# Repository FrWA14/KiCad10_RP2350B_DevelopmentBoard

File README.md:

# Carte de développement RP2350B

Carte basée sur le microcontrôleur RP2350B (QFN-80) de Raspberry Pi, conçue sous KiCad 10.

## Modèle 3D

- [`RP2350.stl`](RP2350.stl) : cliquer dessus pour faire tourner la carte en 3D directement
  sur GitHub.
- [`RP2350.step`](RP2350.step) : modèle complet (carte et composants) pour FreeCAD,
  Fusion 360, SolidWorks, etc.

## Ouvrir le projet

Ouvrir `RP2350.kicad_pro` avec KiCad 10. Le projet est autonome : aucune bibliothèque
à installer.

- `libs/RP2350.kicad_sym` : tous les symboles du schéma.
- `libs/RP2350.pretty` : toutes les empreintes du PCB.
- `libs/3dmodels` : les modèles 3D, liés via `${KIPRJMOD}`.

Les tables `sym-lib-table` et `fp-lib-table` du projet déclarent ces bibliothèques en
chemin relatif.

L'inductance L1 (empreinte 0806) utilise le modèle 3D d'une 0805 (`L_0805_2012Metric`).

## Fabrication

Le dossier `production/` contient les fichiers pour JLCPCB : `RP2350_corrected.zip`
(Gerbers et perçages, avec sérigraphie couleur), `bom.csv`, `positions.csv`, ainsi que
les aperçus des deux faces.

La sérigraphie couleur est générée avec le plugin [Fabrication Toolkit Color](https://github.com/FrWA14/KiCad10_Fabrication-Toolkit-Color). Ses réglages
sont dans `fabrication-toolkit-options.json` et les images sources dans `Image/`.
À la commande : PCB blanc, finition ENIG, option « EasyEDA multi-color silkscreen ».

## Licences des bibliothèques

Le symbole, l'empreinte et le modèle 3D du RP2350B viennent de la bibliothèque
RP2350_KiCad, sous licence GPL v3 (`libs/licences/`). Les autres composants viennent des
bibliothèques officielles de KiCad ou des fabricants.

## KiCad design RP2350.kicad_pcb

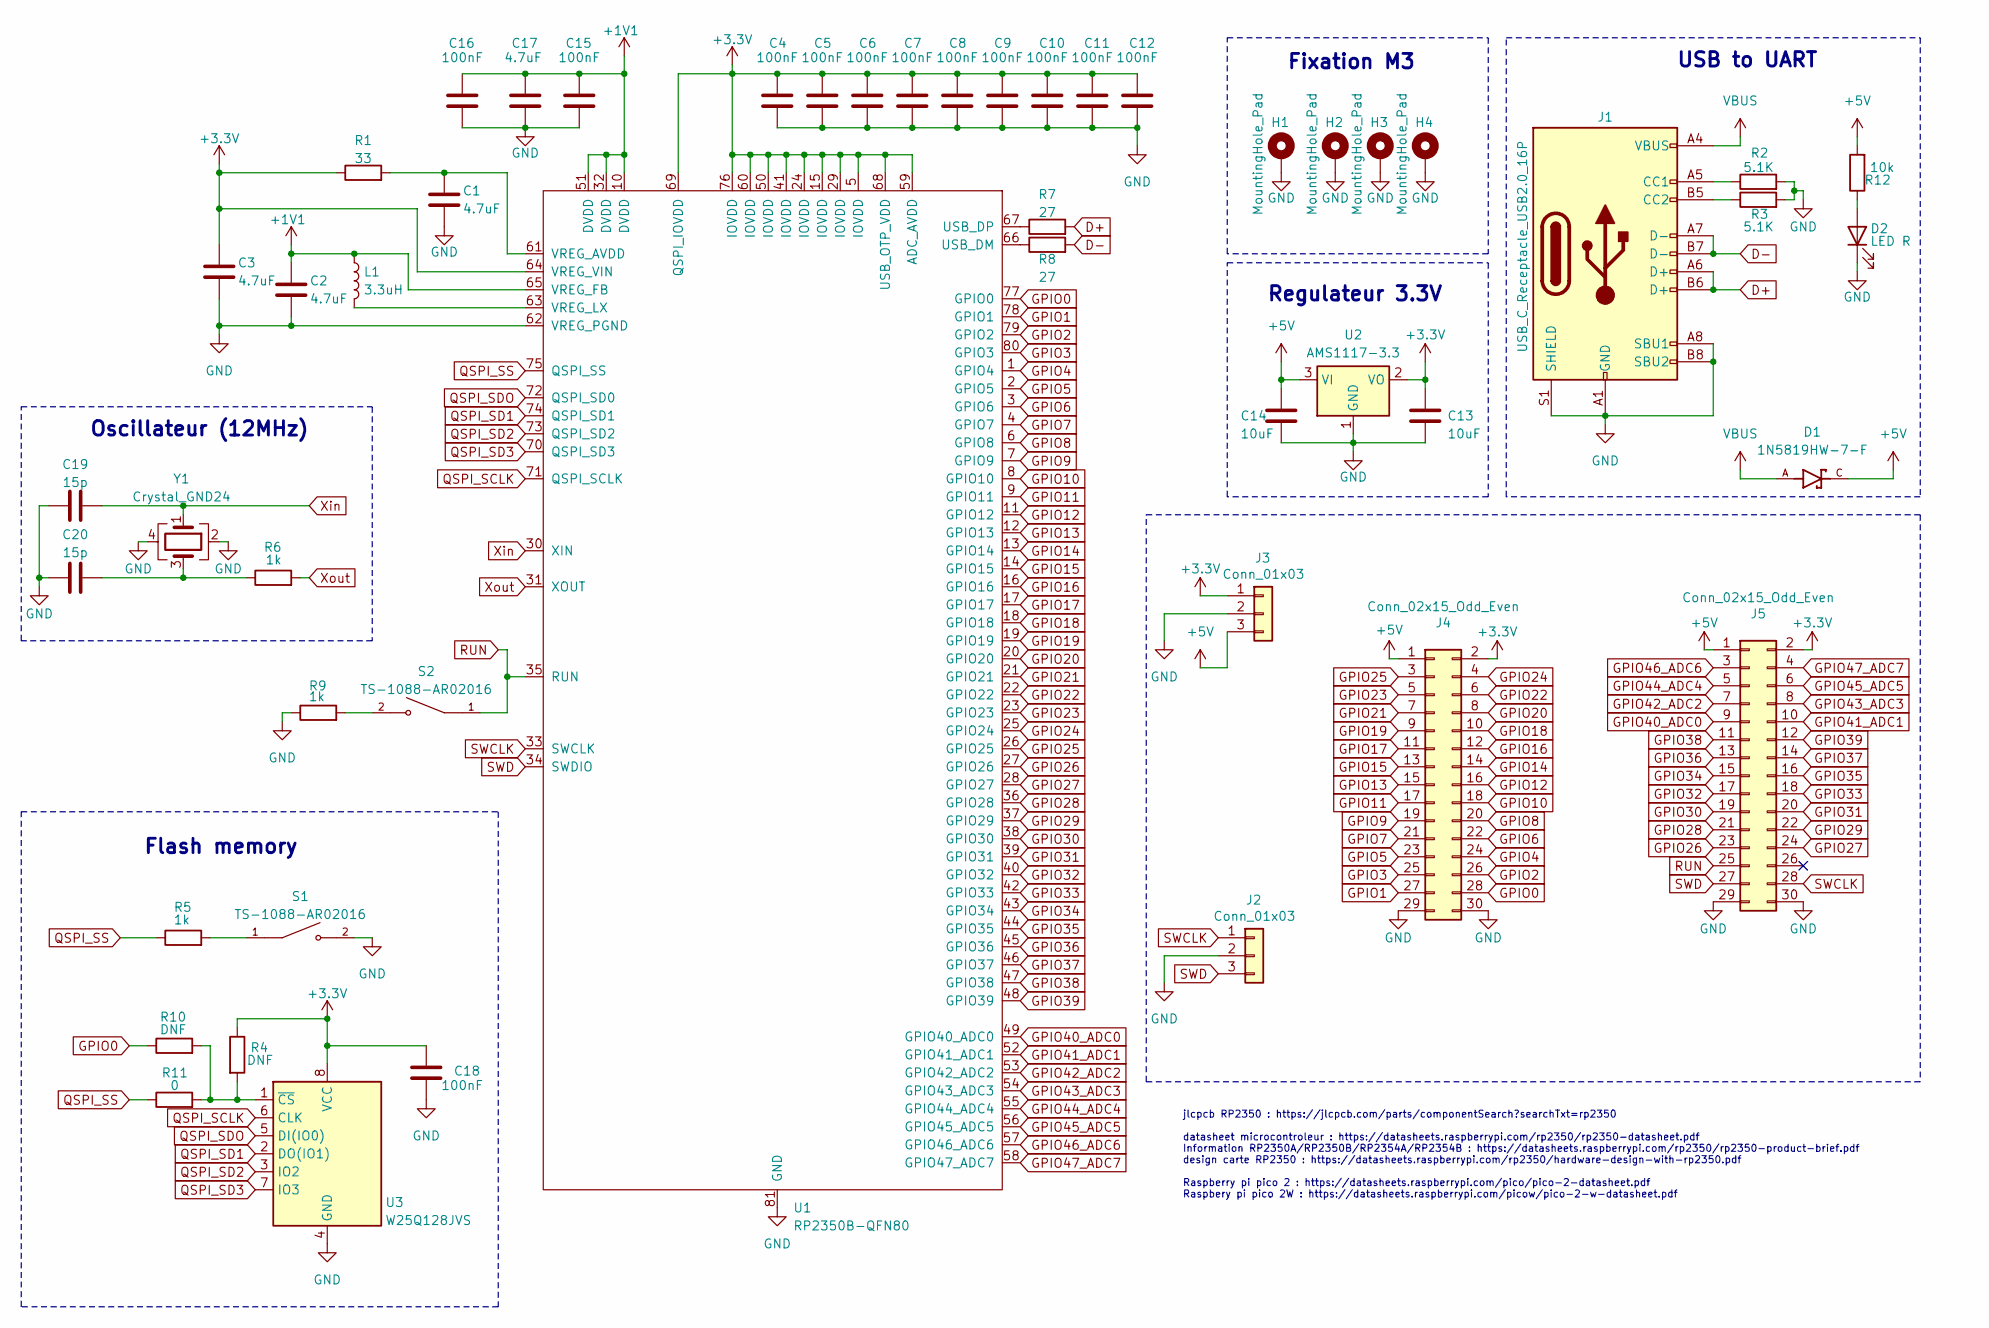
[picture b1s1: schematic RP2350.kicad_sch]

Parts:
C1, C2, C3, C17: 4.7uF; C_0603_1608Metric; JLCPCB Part # C19666
C4, C5, C6, C7, C8, C9, C10, C11, C12, C15, C16, C18: 100nF; C_0603_1608Metric; JLCPCB Part # C14663
C13, C14: 10uF; C_0603_1608Metric; JLCPCB Part # C1691
C19, C20: 15p; C_0603_1608Metric; JLCPCB Part # C1644
D1: 1N5819HW-7-F; D_SOD-123_1N5819HW-7-F; PARTREV 18-2; JLCPCB Part # C82544
D2: LED R; LED_0603_1608Metric; JLCPCB Part # C965799
H1, H2, H3, H4: MountingHole_Pad; MountingHole_3.2mm_M3_Pad_Via
J1: USB_C_Receptacle_USB2.0_16P; USB_C_Receptacle_HCTL_HC-TYPE-C-16P-01A; JLCPCB Part # C393939
J2, J3: Conn_01x03; PinHeader_1x03_P2.54mm_Vertical
J4, J5: Conn_02x15_Odd_Even; IDC-Header_2x15_P2.54mm_Horizontal_vertical; JLCPCB Part # C221084
L1: 3.3uH; L_0806_2016Metric; JLCPCB Part # C42411119
R1: 33; R_0603_1608Metric; JLCPCB Part # C23140
R2, R3: 5.1K; R_0603_1608Metric; JLCPCB Part # C23186
R4, R10: DNF; R_0603_1608Metric
R5, R6, R9: 1k; R_0603_1608Metric; JLCPCB Part # C21190
R7, R8: 27; R_0603_1608Metric; JLCPCB Part # C137753
R11: 0; R_0603_1608Metric; JLCPCB Part # C21189
R12: 10k; R_0603_1608Metric; JLCPCB Part # C25804
S1, S2: TS-1088-AR02016; SW_TS-1088-AR02016; PARTREV N/A; JLCPCB Part # C720477
U1: RP2350B-QFN80; RP2350B_QFN-80_EP_10.573x10.573_Pitch0.4mm; JLCPCB Part # C42415655
U2: AMS1117-3.3; SOT-223-3_TabPin2; JLCPCB Part # C6186
U3: W25Q128JVS; SOIC-8_5.23x5.23mm_P1.27mm; JLCPCB Part # C97521
Y1: Crystal_GND24; Crystal_SMD_3225-4Pin_3.2x2.5mm; JLCPCB Part # C20625731

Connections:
+1V1: C2.1, C15.1, C16.1, C17.1, L1.1, U1.10 (DVDD), U1.32 (DVDD), U1.51 (DVDD), U1.65 (VREG_FB)
+3.3V: C3.1, C4.1, C5.1, C6.1, C7.1, C8.1, C9.1, C10.1, C11.1, C12.1, C13.1, C18.1, J3.1, J4.2, J5.2, R1.1, R4.1, U1.5 (IOVDD), U1.15 (IOVDD), U1.24 (IOVDD), U1.29 (IOVDD), U1.41 (IOVDD), U1.50 (IOVDD), U1.59 (ADC_AVDD), U1.60 (IOVDD), U1.64 (VREG_VIN), U1.68 (USB_OTP_VDD), U1.69 (QSPI_IOVDD), U1.76 (IOVDD), U2.2 (VO), U3.8 (VCC)
+5V: C14.1, D1.C, J3.3, J4.1, J5.1, R12.2, U2.3 (VI)
D+: J1.A6 (D+), J1.B6 (D+), R7.2
D-: J1.A7 (D-), J1.B7 (D-), R8.2
GND: C1.2, C2.2, C3.2, C4.2, C5.2, C6.2, C7.2, C8.2, C9.2, C10.2, C11.2, C12.2, C13.2, C14.2, C15.2, C16.2, C17.2, C18.2, C19.1, C20.1, D2.1 (K), H1.1 (1_1), H2.1 (1_1), H3.1 (1_1), H4.1 (1_1), J1.A1 (GND), J1.A8 (SBU1), J1.A12 (GND), J1.B1 (GND), J1.B8 (SBU2), J1.B12 (GND), J1.S1 (SHIELD), J2.2, J3.2, J4.29, J4.30, J5.29, J5.30, R2.2, R3.2, R9.1, S1.2, U1.62 (VREG_PGND), U1.81 (GND), U2.1 (GND), U3.4 (GND), Y1.2, Y1.4
GPIO0: J4.28, R10.1, U1.77 (GPIO0)
GPIO1: J4.27, U1.78 (GPIO1)
GPIO2: J4.26, U1.79 (GPIO2)
GPIO3: J4.25, U1.80 (GPIO3)
GPIO4: J4.24, U1.1 (GPIO4)
GPIO5: J4.23, U1.2 (GPIO5)
GPIO6: J4.22, U1.3 (GPIO6)
GPIO7: J4.21, U1.4 (GPIO7)
GPIO8: J4.20, U1.6 (GPIO8)
GPIO9: J4.19, U1.7 (GPIO9)
GPIO10: J4.18, U1.8 (GPIO10)
GPIO11: J4.17, U1.9 (GPIO11)
GPIO12: J4.16, U1.11 (GPIO12)
GPIO13: J4.15, U1.12 (GPIO13)
GPIO14: J4.14, U1.13 (GPIO14)
GPIO15: J4.13, U1.14 (GPIO15)
GPIO16: J4.12, U1.16 (GPIO16)
GPIO17: J4.11, U1.17 (GPIO17)
GPIO18: J4.10, U1.18 (GPIO18)
GPIO19: J4.9, U1.19 (GPIO19)
GPIO20: J4.8, U1.20 (GPIO20)
GPIO21: J4.7, U1.21 (GPIO21)
GPIO22: J4.6, U1.22 (GPIO22)
GPIO23: J4.5, U1.23 (GPIO23)
GPIO24: J4.4, U1.25 (GPIO24)
GPIO25: J4.3, U1.26 (GPIO25)
GPIO26: J5.23, U1.27 (GPIO26)
GPIO27: J5.24, U1.28 (GPIO27)
GPIO28: J5.21, U1.36 (GPIO28)
GPIO29: J5.22, U1.37 (GPIO29)
GPIO30: J5.19, U1.38 (GPIO30)
GPIO31: J5.20, U1.39 (GPIO31)
GPIO32: J5.17, U1.40 (GPIO32)
GPIO33: J5.18, U1.42 (GPIO33)
GPIO34: J5.15, U1.43 (GPIO34)
GPIO35: J5.16, U1.44 (GPIO35)
GPIO36: J5.13, U1.45 (GPIO36)
GPIO37: J5.14, U1.46 (GPIO37)
GPIO38: J5.11, U1.47 (GPIO38)
GPIO39: J5.12, U1.48 (GPIO39)
GPIO40_ADC0: J5.9, U1.49 (GPIO40_ADC0)
GPIO41_ADC1: J5.10, U1.52 (GPIO41_ADC1)
GPIO42_ADC2: J5.7, U1.53 (GPIO42_ADC2)
GPIO43_ADC3: J5.8, U1.54 (GPIO43_ADC3)
GPIO44_ADC4: J5.5, U1.55 (GPIO44_ADC4)
GPIO45_ADC5: J5.6, U1.56 (GPIO45_ADC5)
GPIO46_ADC6: J5.3, U1.57 (GPIO46_ADC6)
GPIO47_ADC7: J5.4, U1.58 (GPIO47_ADC7)
unnamed: C20.2, R6.1, Y1.3
unnamed: D2.2 (A), R12.1
unnamed: J1.A5 (CC1), R2.1
unnamed: J1.B5 (CC2), R3.1
unnamed: R5.2, S1.1
unnamed: R9.2, S2.2
unnamed: R8.1, U1.66 (USB_DM)
unnamed: R7.1, U1.67 (USB_DP)
unnamed: C1.1, R1.2, U1.61 (VREG_AVDD)
unnamed: L1.2, U1.63 (VREG_LX)
unnamed: R4.2, R10.2, R11.2, U3.1 (~CS)
QSPI_SCLK: U1.71 (QSPI_SCLK), U3.6 (CLK)
QSPI_SD1: U1.74 (QSPI_SD1), U3.2 (DO(IO1))
QSPI_SD2: U1.73 (QSPI_SD2), U3.3 (IO2)
QSPI_SD3: U1.70 (QSPI_SD3), U3.7 (IO3)
QSPI_SDO: U1.72 (QSPI_SD0), U3.5 (DI(IO0))
QSPI_SS: R5.1, R11.1, U1.75 (QSPI_SS)
RUN: J5.25, S2.1, U1.35 (RUN)
SWCLK: J2.1, J5.28, U1.33 (SWCLK)
SWD: J2.3, J5.27, U1.34 (SWDIO)
VBUS: D1.A, J1.A4 (VBUS), J1.A9 (VBUS), J1.B4 (VBUS), J1.B9 (VBUS)
Xin: C19.2, U1.30 (XIN), Y1.1
Xout: R6.2, U1.31 (XOUT)

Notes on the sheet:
USB to UART
Flash memory
jlcpcb RP2350 : https://jlcpcb.com/parts/componentSearch?searchTxt=rp2350 datasheet microcontroleur : https://datasheets.raspberrypi.com/rp2350/rp2350-datasheet.pdf Information RP2350A/RP2350B/RP2354A/RP2354B : https://datasheets.raspberrypi.com/rp2350/rp2350-product-brief.pdf design carte RP2350 :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
Fixation M3
Regulateur 3.3V
Oscillateur (12MHz)

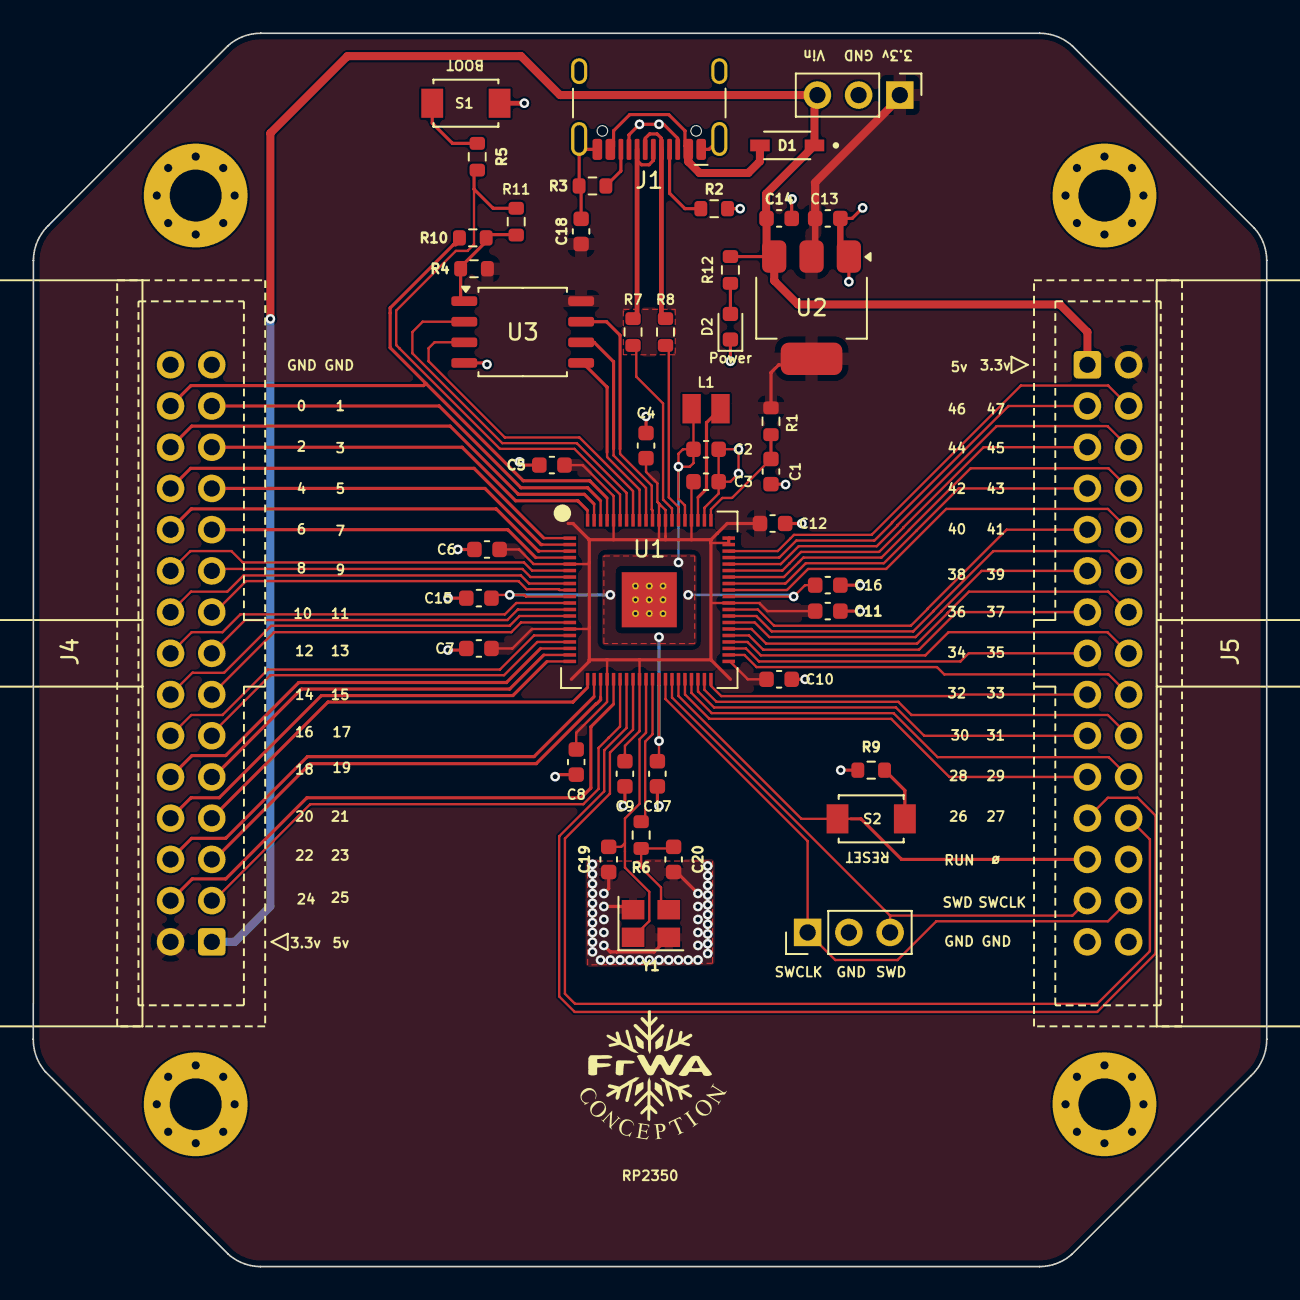
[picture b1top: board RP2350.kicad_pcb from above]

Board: 2 copper layers, 76.0 x 76.0 mm, 50 parts (0 on the bottom side), 77 nets.

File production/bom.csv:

Designator,Footprint,Quantity,Value,LCSC Part #
"C1, C17, C2, C3",0603,4,4.7uF,C19666
"C10, C11, C12, C15, C16, C18, C4, C5, C6, C7, C8, C9",0603,12,100nF, C14663
"C13, C14",0603,2,10uF,C1691
"C19, C20",0603,2,15p, C1644
D1,D_SOD-123_1N5819HW-7-F,1,1N5819HW-7-F, C82544
D2,0603,1,LED R, C965799
J1,USB_C_Receptacle_HCTL_HC-TYPE-C-16P-01A,1,USB_C_Receptacle_USB2.0_16P,C393939
"J2, J3",PinHeader_1x03_P2.54mm_Vertical,2,Conn_01x03,
"J4, J5",IDC-Header_2x15_P2.54mm_Horizontal_vertical,2,Conn_02x15_Odd_Even,C221084
L1,0806,1,3.3uH,C42411119
R1,0603,1,33, C23140
"R10, R4",0603,2,DNF,
R11,0603,1,0, C21189
R12,0603,1,10k, C25804
"R2, R3",0603,2,5.1K,C23186
"R5, R6, R9",0603,3,1k,C21190
"R7, R8",0603,2,27,C137753
"S1, S2",SW_TS-1088-AR02016,2,TS-1088-AR02016,C720477
U1,RP2350B_QFN-80_EP_10.573x10.573_Pitch0.4mm,1,RP2350B-QFN80,C42415655
U2,SOT-223-3_TabPin2,1,AMS1117-3.3,C6186
U3,SOIC-8_5.23x5.23mm_P1.27mm,1,W25Q128JVS,C97521
Y1,Crystal_SMD_3225-4Pin_3.2x2.5mm,1,Crystal_GND24,C20625731
